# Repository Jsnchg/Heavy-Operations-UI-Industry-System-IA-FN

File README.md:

# Heavy-Operations-UI-Industry-System-IA-FN

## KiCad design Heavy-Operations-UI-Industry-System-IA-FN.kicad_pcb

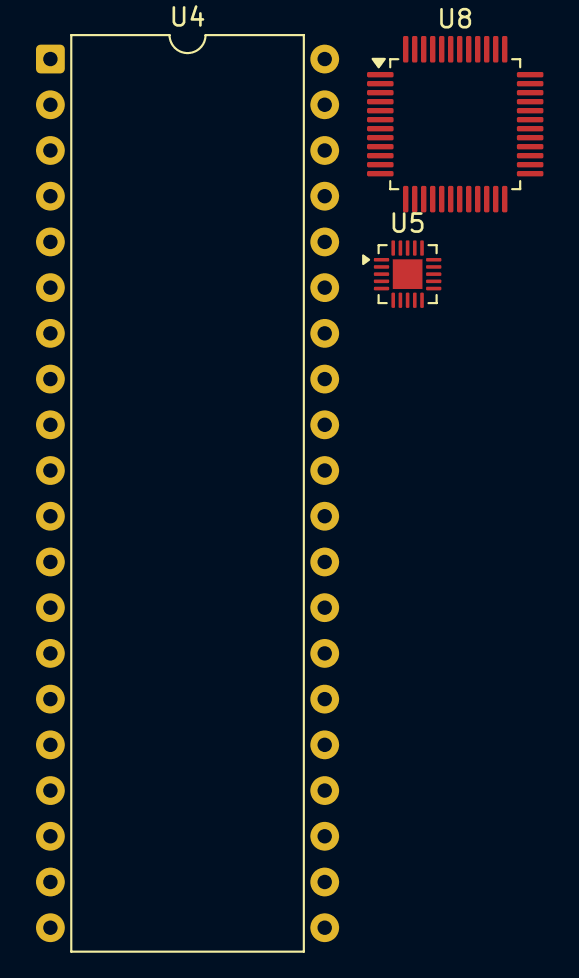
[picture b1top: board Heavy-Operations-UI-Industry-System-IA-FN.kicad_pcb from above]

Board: 2 copper layers, 3 parts (0 on the bottom side), 5 nets, no tracks yet.

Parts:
U4: 8080; DIP-40_W15.24mm
U5: CH246D; QFN-20-1EP_3x3mm_P0.4mm_EP1.65x1.65mm
U8: DP83848C; LQFP-48_7x7mm_P0.5mm

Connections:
unnamed: U4.11 (-5V), U5.2 (VHV)
unnamed: U4.2 (GND), U5.7 (VDD)
unnamed: U8.15 (AGND), U8.19 (AGND)
unnamed: U8.35 (IOGND), U8.47 (IOGND)
unnamed: U8.32 (IOVDD33), U8.48 (IOVDD33)

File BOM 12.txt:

Heavy-Operations-UI-Industry-System-IA-FN
BOM 12

A. Factory Network
1. VDC
2. CAT24C256
3. FXLA108
4. SG3525A
5. 8080
6. RSL15
7. CH246D
8. NCP45496
9. FPF2003
10. DP83848C
11. D_Filled X4
12. ESDONCAN1LT 

Note:
Component 7 was added to make the project more unique
